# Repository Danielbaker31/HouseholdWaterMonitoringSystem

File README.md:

https://danielbaker31.github.io/HouseholdWaterMonitoringSystem/

This is a work in progress.

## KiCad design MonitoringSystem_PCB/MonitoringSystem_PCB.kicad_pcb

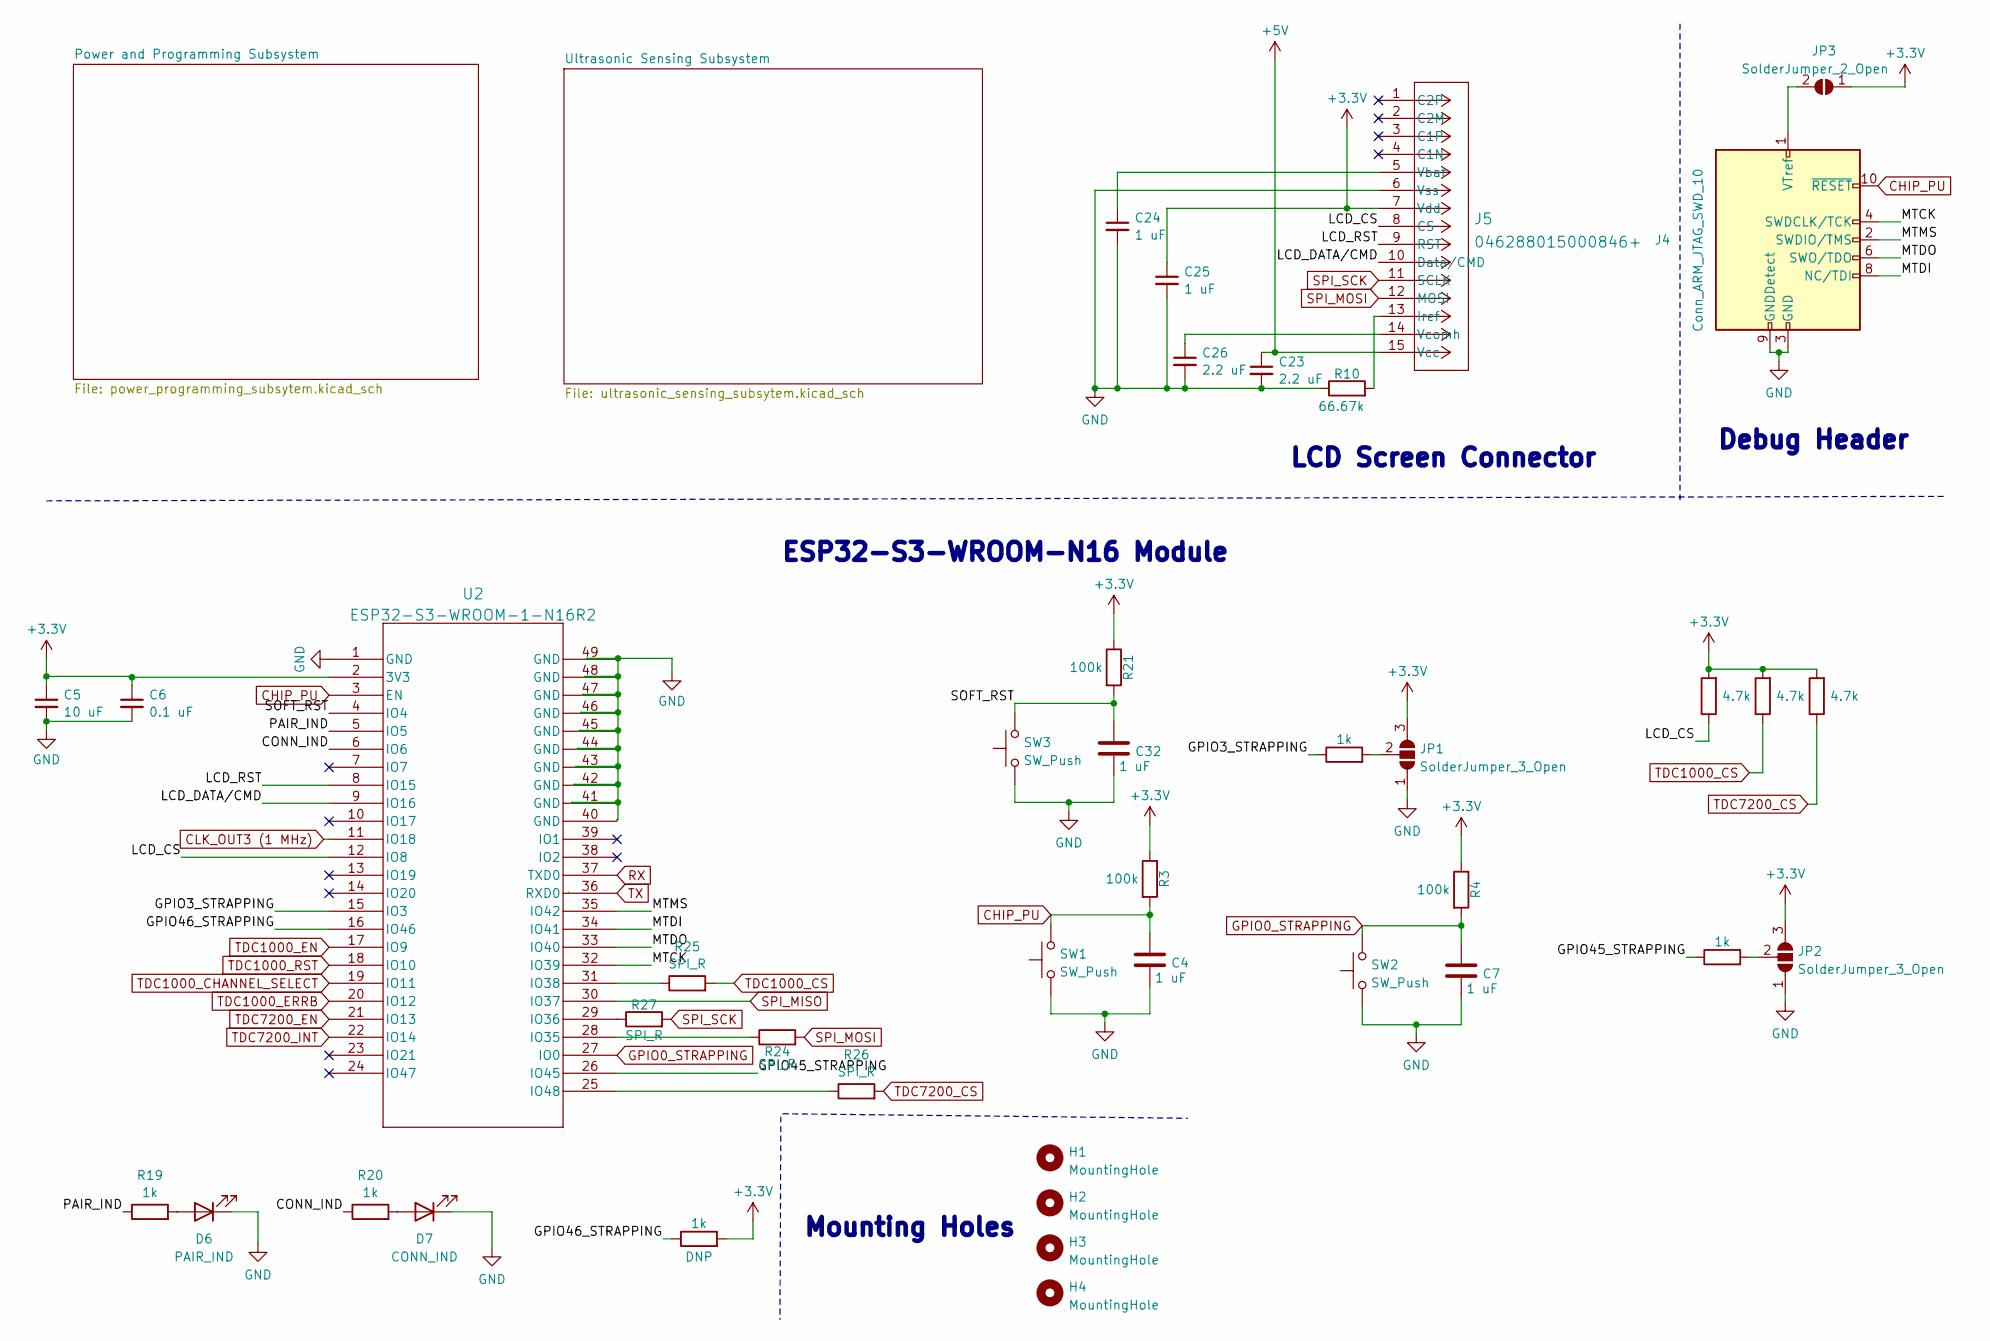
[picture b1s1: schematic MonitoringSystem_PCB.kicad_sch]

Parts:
C4, C7, C24, C25, C32: 1 uF; C_0805_2012Metric
C5: 10 uF; C_0805_2012Metric
C6: 0.1 uF; C_0805_2012Metric
C23, C26: 2.2 uF; C_0805_2012Metric
D6: PAIR_IND; LED_0805_2012Metric
D7: CONN_IND; LED_0805_2012Metric
H1, H2, H3, H4: MountingHole; MountingHole_3.2mm_M3
J4: Conn_ARM_JTAG_SWD_10; IDC-Header_2x05_P2.54mm_Vertical
J5: 046288015000846+; 15Pin_TAB
JP1, JP2: SolderJumper_3_Open; SolderJumper-3_P2.0mm_Open_TrianglePad1.0x1.5mm
JP3: SolderJumper_2_Open; SolderJumper-2_P1.3mm_Open_TrianglePad1.0x1.5mm
R3, R4, R21: 100k; R_0805_2012Metric
R5, R6, R9, R19, R20: 1k; R_0805_2012Metric
R10: 66.67k; R_0805_2012Metric
R11, R12, R13: 4.7k; R_0805_2012Metric
R24, R25, R26, R27: SPI_R; R_0805_2012Metric
SW1, SW2, SW3: SW_Push; SW_SPST_B3S-1000
U2: ESP32-S3-WROOM-1-N16R2; ESP32-S3-WROOM-1_EXP

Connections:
+3.3V: C5.1, C6.1, C25.1, J5.7 (Vdd), JP1.3 (B), JP2.3 (B), JP3.1 (A), R3.1, R4.1, R6.2, R11.2, R12.2, R13.2, R21.1, U2.2 (3V3); also elsewhere on the board
+5V: C23.1, J5.15 (Vcc); also elsewhere on the board
/CONN_IND: R20.1, U2.6 (IO6)
/GPIO3_STRAPPING: R5.1, U2.15 (IO3)
/GPIO45_STRAPPING: R9.1, U2.26 (IO45)
/GPIO46_STRAPPING: R6.1, U2.16 (IO46)
/LCD_CS: J5.8 (CS), R11.1, U2.12 (IO8)
/LCD_DATA/CMD: J5.10 (Data/CMD), U2.9 (IO16)
/LCD_RST: J5.9 (RST), U2.8 (IO15)
/MTCK: J4.4 (SWDCLK/TCK), U2.32 (IO39)
/MTDI: J4.8 (NC/TDI), U2.34 (IO41)
/MTDO: J4.6 (SWO/TDO), U2.33 (IO40)
/MTMS: J4.2 (SWDIO/TMS), U2.35 (IO42)
/PAIR_IND: R19.1, U2.5 (IO5)
/SOFT_RST: C32.1, R21.2, SW3.2, U2.4 (IO4)
CHIP_PU: C4.1, J4.10 (~RESET), R3.2, SW1.2, U2.3 (EN); also elsewhere on the board
CLK_OUT3 (1 MHz): U2.11 (IO18); also elsewhere on the board
GND: C4.2, C5.2, C6.2, C7.2, C23.2, C24.2, C25.2, C26.2, C32.2, D6.1 (K), D7.1 (K), J4.3 (GND), J4.5 (GND), J4.9 (GNDDetect), J5.6 (Vss), JP1.1 (A), JP2.1 (A), R10.1, SW1.1, SW2.1, SW3.1, U2.1 (GND), U2.40 (GND), U2.41 (GND), U2.42 (GND), U2.43 (GND), U2.44 (GND), U2.45 (GND), U2.46 (GND), U2.47 (GND), U2.48 (GND), U2.49 (GND); also elsewhere on the board
GPIO0_STRAPPING: C7.1, R4.2, SW2.2, U2.27 (IO0); also elsewhere on the board
unnamed: D6.2 (A), R19.2
unnamed: D7.2 (A), R20.2
unnamed: J4.1 (VTref), JP3.2 (B)
unnamed: J5.13 (Iref), R10.2
unnamed: C24.1, J5.5 (Vbat)
unnamed: C26.1, J5.14 (Vcomh)
unnamed: JP1.2 (C), R5.2
unnamed: JP2.2 (C), R9.2
unnamed: R24.1, U2.28 (IO35)
unnamed: R27.1, U2.29 (IO36)
unnamed: R25.1, U2.31 (IO38)
unnamed: R26.1, U2.25 (IO48)
RX: U2.37 (TXD0); also elsewhere on the board
SPI_MISO: U2.30 (IO37); also elsewhere on the board
SPI_MOSI: J5.12 (MOSI), R24.2; also elsewhere on the board
SPI_SCK: J5.11 (SCLK), R27.2; also elsewhere on the board
TDC1000_CHANNEL_SELECT: U2.19 (IO11); also elsewhere on the board
TDC1000_CS: R12.1, R25.2; also elsewhere on the board
TDC1000_EN: U2.17 (IO9); also elsewhere on the board
TDC1000_ERRB: U2.20 (IO12); also elsewhere on the board
TDC1000_RST: U2.18 (IO10); also elsewhere on the board
TDC7200_CS: R13.1, R26.2; also elsewhere on the board
TDC7200_EN: U2.21 (IO13); also elsewhere on the board
TDC7200_INT: U2.22 (IO14); also elsewhere on the board
TX: U2.36 (RXD0); also elsewhere on the board

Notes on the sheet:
Mounting Holes
LCD Screen Connector
Debug Header
ESP32-S3-WROOM-N16 Module

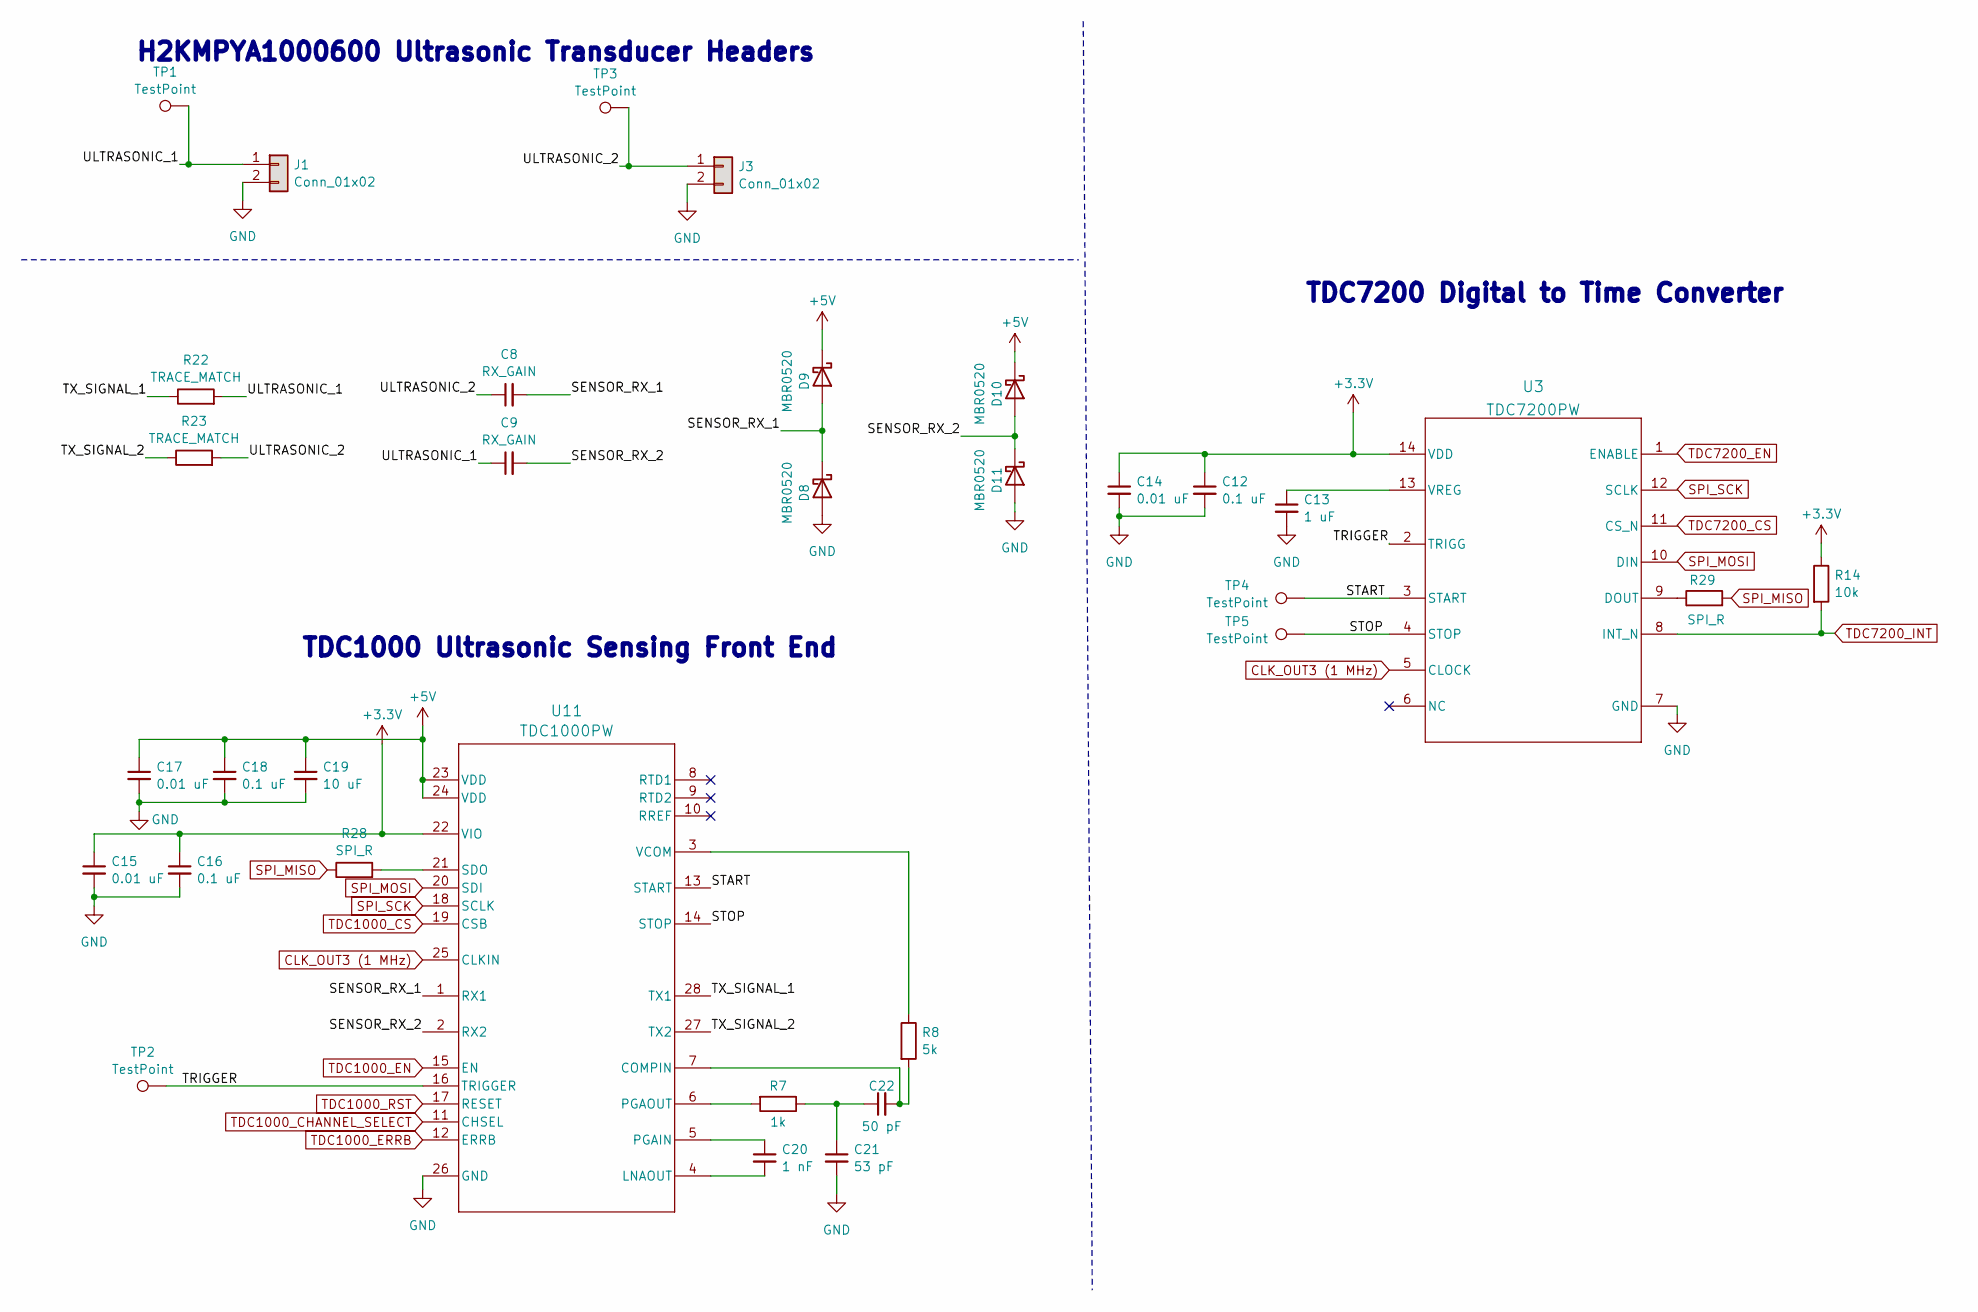
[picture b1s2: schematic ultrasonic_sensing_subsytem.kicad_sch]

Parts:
C8, C9: RX_GAIN; C_0805_2012Metric
C12, C16, C18: 0.1 uF; C_0805_2012Metric
C13: 1 uF; C_0805_2012Metric
C14, C15, C17: 0.01 uF; C_0805_2012Metric
C19: 10 uF; C_0805_2012Metric
C20: 1 nF; C_0805_2012Metric
C21: 53 pF; C_0805_2012Metric
C22: 50 pF; C_0805_2012Metric
D8, D9, D10, D11: MBR0520; D_SOD-123
J1, J3: Conn_01x02; Molex_KK-254_AE-6410-02A_1x02_P2.54mm_Vertical
R7: 1k; R_0805_2012Metric
R8: 5k; R_0805_2012Metric
R14: 10k; R_0805_2012Metric
R22, R23: TRACE_MATCH; R_0805_2012Metric
R28, R29: SPI_R; R_0805_2012Metric
TP1, TP2, TP3, TP4, TP5: TestPoint; TestPoint_Keystone_5010-5014_Multipurpose
U3: TDC7200PW; PW0014A_N
U11: TDC1000PW; PW0028A_N

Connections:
+3.3V: C12.1, C14.1, C15.1, C16.1, R14.1, U3.14 (VDD), U11.22 (VIO); also elsewhere on the board
+5V: C17.1, C18.1, C19.1, D9.1 (K), D10.1 (K), U11.23 (VDD), U11.24 (VDD); also elsewhere on the board
/Ultrasonic Sensing Subsystem/SENSOR_RX_1: C8.2, D8.1 (K), D9.2 (A), U11.1 (RX1)
/Ultrasonic Sensing Subsystem/SENSOR_RX_2: C9.2, D10.2 (A), D11.1 (K), U11.2 (RX2)
/Ultrasonic Sensing Subsystem/START: TP4.1, U3.3 (START), U11.13 (START)
/Ultrasonic Sensing Subsystem/STOP: TP5.1, U3.4 (STOP), U11.14 (STOP)
/Ultrasonic Sensing Subsystem/TRIGGER: TP2.1, U3.2 (TRIGG), U11.16 (TRIGGER)
/Ultrasonic Sensing Subsystem/TX_SIGNAL_1: R22.1, U11.28 (TX1)
/Ultrasonic Sensing Subsystem/TX_SIGNAL_2: R23.1, U11.27 (TX2)
/Ultrasonic Sensing Subsystem/ULTRASONIC_1: C9.1, J1.1, R22.2, TP1.1
/Ultrasonic Sensing Subsystem/ULTRASONIC_2: C8.1, J3.1, R23.2, TP3.1
CLK_OUT3 (1 MHz): U3.5 (CLOCK), U11.25 (CLKIN); also elsewhere on the board
GND: C12.2, C13.2, C14.2, C15.2, C16.2, C17.2, C18.2, C19.2, C21.2, D8.2 (A), D11.2 (A), J1.2, J3.2, U3.7 (GND), U11.26 (GND); also elsewhere on the board
unnamed: C21.1, C22.1, R7.1
unnamed: R29.1, U3.9 (DOUT)
unnamed: C13.1, U3.13 (VREG)
unnamed: C22.2, R8.2, U11.7 (COMPIN)
unnamed: C20.2, U11.4 (LNAOUT)
unnamed: C20.1, U11.5 (PGAIN)
unnamed: R7.2, U11.6 (PGAOUT)
unnamed: R28.2, U11.21 (SDO)
unnamed: R8.1, U11.3 (VCOM)
SPI_MISO: R28.1, R29.2; also elsewhere on the board
SPI_MOSI: U3.10 (DIN), U11.20 (SDI); also elsewhere on the board
SPI_SCK: U3.12 (SCLK), U11.18 (SCLK); also elsewhere on the board
TDC1000_CHANNEL_SELECT: U11.11 (CHSEL); also elsewhere on the board
TDC1000_CS: U11.19 (CSB); also elsewhere on the board
TDC1000_EN: U11.15 (EN); also elsewhere on the board
TDC1000_ERRB: U11.12 (ERRB); also elsewhere on the board
TDC1000_RST: U11.17 (RESET); also elsewhere on the board
TDC7200_CS: U3.11 (CS_N); also elsewhere on the board
TDC7200_EN: U3.1 (ENABLE); also elsewhere on the board
TDC7200_INT: R14.2, U3.8 (INT_N); also elsewhere on the board

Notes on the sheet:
H2KMPYA1000600 Ultrasonic Transducer Headers
TDC7200 Digital to Time Converter
TDC1000 Ultrasonic Sensing Front End

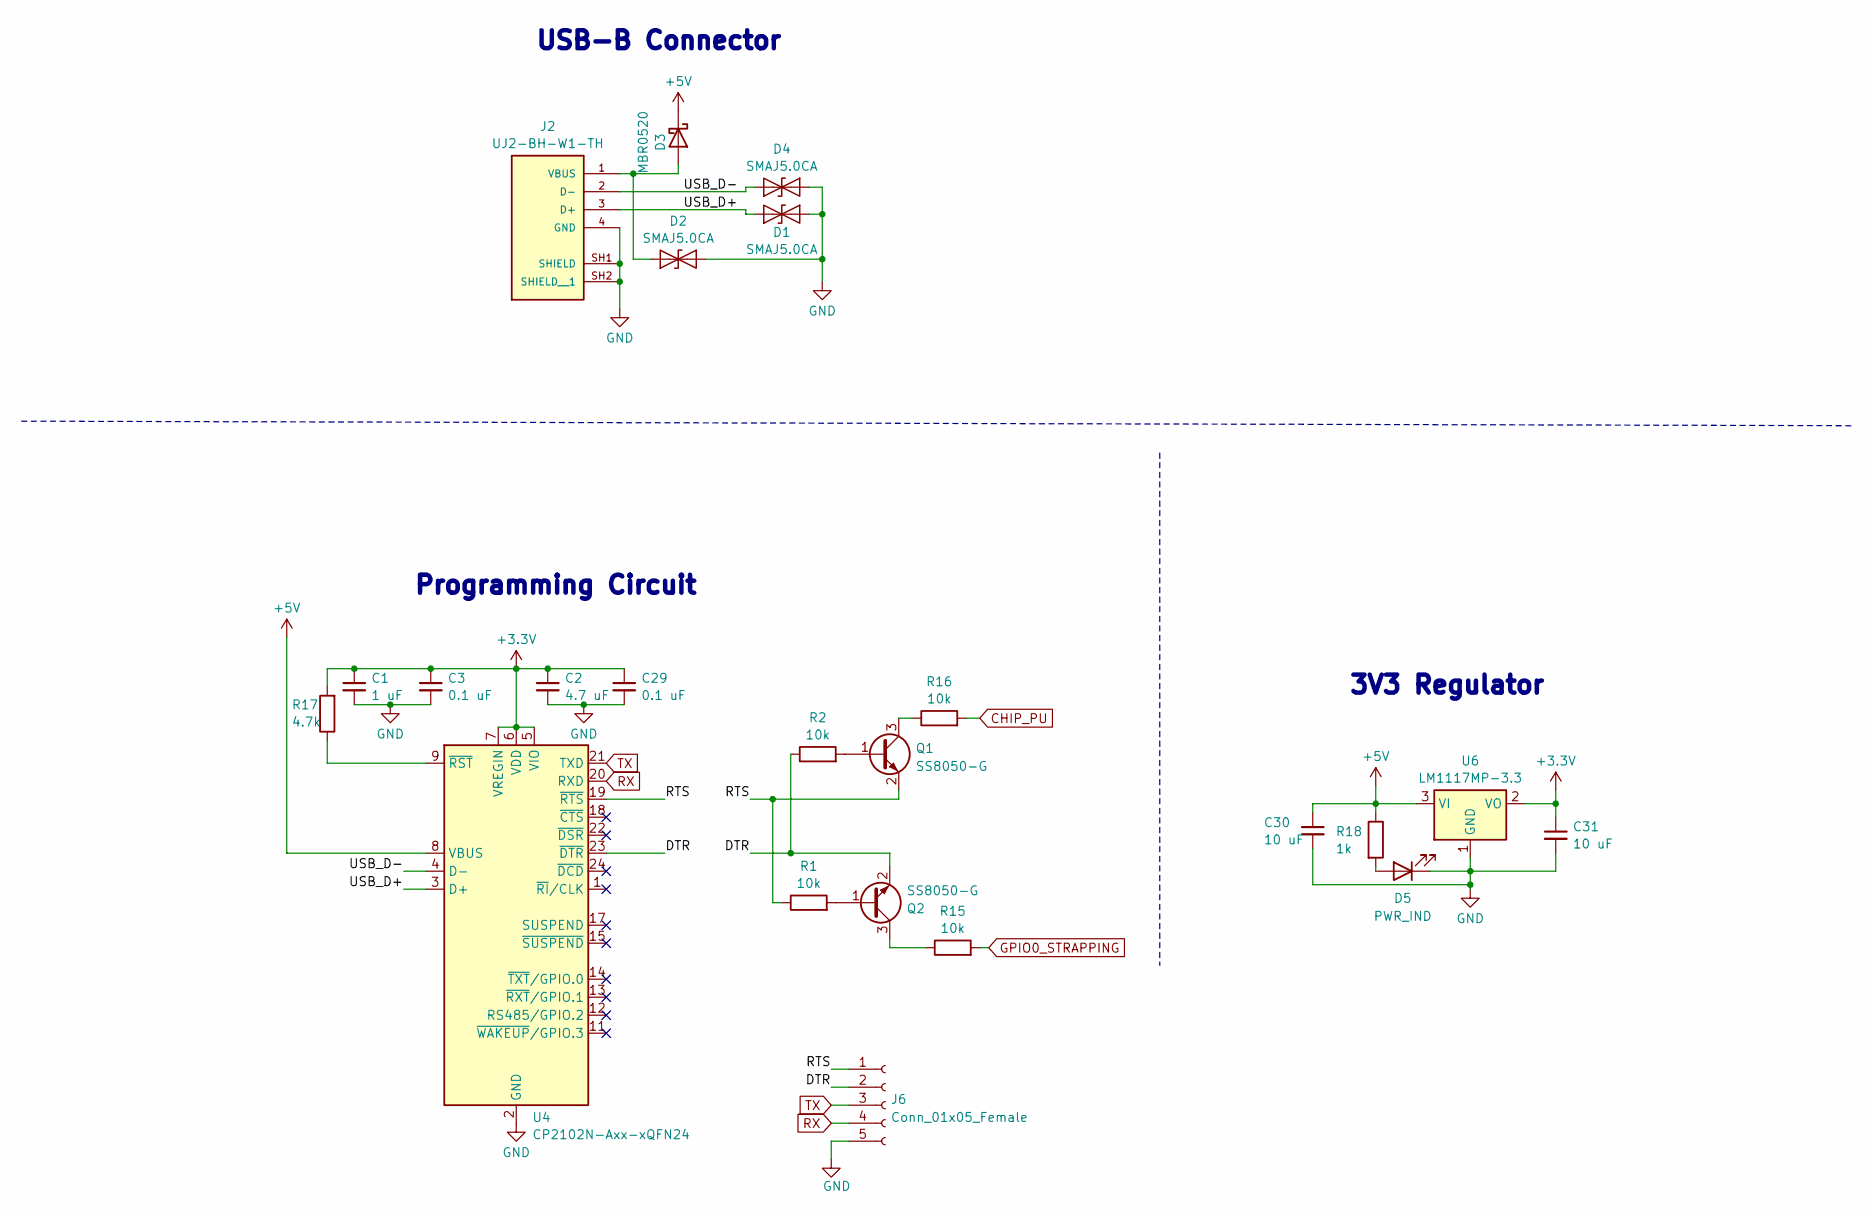
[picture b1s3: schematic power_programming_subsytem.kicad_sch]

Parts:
C1: 1 uF; C_0805_2012Metric
C2: 4.7 uF; C_0805_2012Metric
C3, C29: 0.1 uF; C_0805_2012Metric
C30, C31: 10 uF; C_0805_2012Metric
D1, D2, D4: SMAJ5.0CA; D_SMA
D3: MBR0520; D_SOD-123
D5: PWR_IND; LED_0805_2012Metric
J2: UJ2-BH-W1-TH; CUI_UJ2-BH-W1-TH; PART_REV 1.0
J6: Conn_01x05_Female; PinHeader_1x05_P2.54mm_Vertical
Q1, Q2: SS8050-G; SOT-23
R1, R2, R15, R16: 10k; R_0805_2012Metric
R17: 4.7k; R_0805_2012Metric
R18: 1k; R_0805_2012Metric
U4: CP2102N-Axx-xQFN24; QFN-24-1EP_4x4mm_P0.5mm_EP2.6x2.6mm
U6: LM1117MP-3.3; SOT-223-3_TabPin2

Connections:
+3.3V: C1.1, C2.1, C3.1, C29.1, C31.1, R17.2, U4.5 (VIO), U4.6 (VDD), U4.7 (VREGIN), U6.2 (VO); also elsewhere on the board
+5V: C30.1, D3.1 (K), R18.1, U4.8 (VBUS), U6.3 (VI); also elsewhere on the board
/Power and Programming Subsystem/DTR: J6.2, Q2.2 (E), R2.1, U4.23 (~DTR)
/Power and Programming Subsystem/RTS: J6.1, Q1.2 (E), R1.1, U4.19 (~RTS)
/Power and Programming Subsystem/USB_D+: D1.1 (A1), J2.3 (D+), U4.3 (D+)
/Power and Programming Subsystem/USB_D-: D4.1 (A1), J2.2 (D-), U4.4 (D-)
CHIP_PU: R16.2; also elsewhere on the board
GND: C1.2, C2.2, C3.2, C29.2, C30.2, C31.2, D1.2 (A2), D2.2 (A2), D4.2 (A2), D5.1 (K), J2.4 (GND), J2.SH1 (SHIELD), J2.SH2 (SHIELD__1), J6.5, U4.2 (GND), U4.25 (GND), U6.1 (GND); also elsewhere on the board
GPIO0_STRAPPING: R15.2; also elsewhere on the board
unnamed: D2.1 (A1), D3.2 (A), J2.1 (VBUS)
unnamed: D5.2 (A), R18.2
unnamed: Q1.1 (B), R2.2
unnamed: Q1.3 (C), R16.1
unnamed: Q2.1 (B), R1.2
unnamed: Q2.3 (C), R15.1
unnamed: R17.1, U4.9 (~RST)
RX: J6.4, U4.20 (RXD); also elsewhere on the board
TX: J6.3, U4.21 (TXD); also elsewhere on the board

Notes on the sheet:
Programming Circuit
3V3 Regulator
USB-B Connector

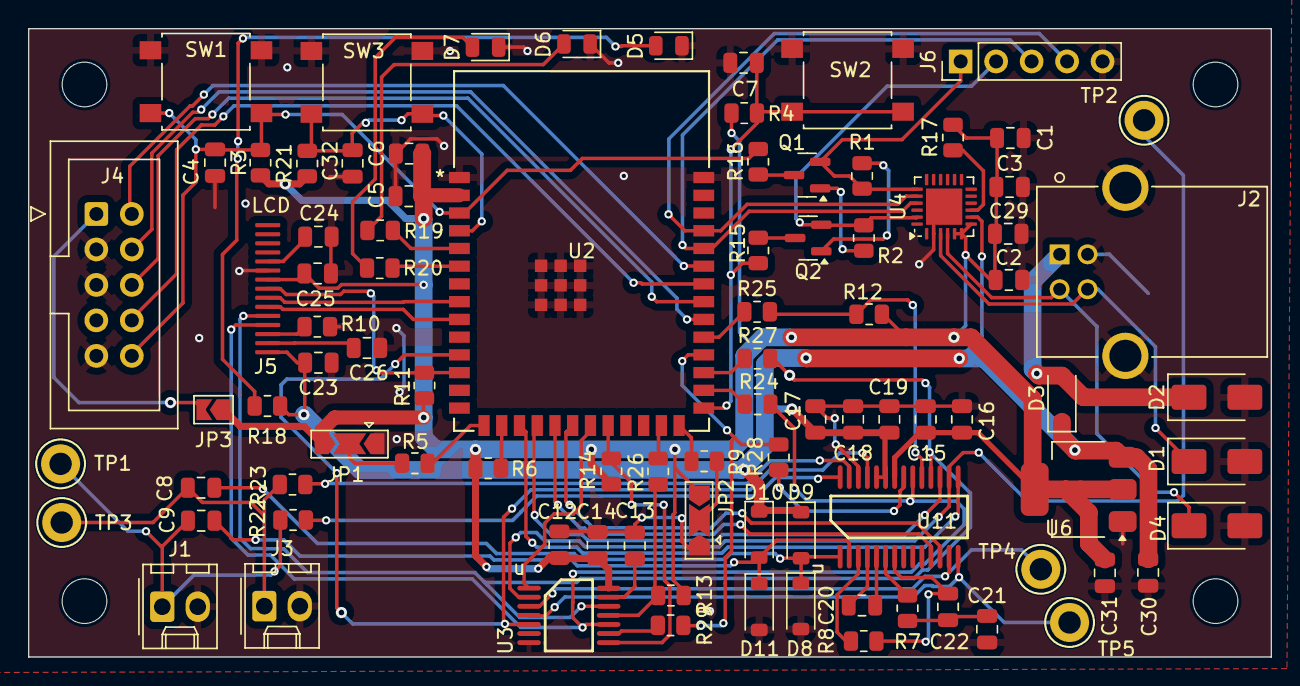
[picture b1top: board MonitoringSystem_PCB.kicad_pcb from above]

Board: 2 copper layers, 89.0 x 45.0 mm, 96 parts (0 on the bottom side), 73 nets.

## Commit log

2024-10-01 daniels journal
2024-10-02 drbaker5 journal thru 10/1
2024-10-02 week change
2024-10-09 adding advait journal
2024-10-10 github pages test
2024-10-10 moved index out of subfolder
2024-10-10 Create README.md
    added the website to the readme
2024-10-10 Mock Front End to test GET request
2024-10-10 updating display bug
2024-10-10 bug logging to see what's eerror
2024-10-10 fixing double parsing error
2024-10-11 first draft of pcb schematic
2024-10-11 modified parts' pinouts
2024-10-11 fix from backup
2024-10-11 redid project bc kicad is braindead
2024-10-11 schematic changes
2024-10-11 delete
2024-10-11 schematic updates
2024-10-15 finish first draft of schematic of PCB
2024-10-15 pushing complete frontend changes
2024-10-15 added multiple device registrion
2024-10-15 switched micro-usb for usb-b, started pcb
2024-10-15 minor change to usb-uart bridge
2024-10-15 fixed capitlaization bug
2024-10-15 fixing file name issues
2024-10-16 pcb done
2024-10-16 DRC error stuff
2024-10-16 finalized pcb, fixed eroors, generated gerber
2024-10-16 test commit
2024-10-17 Working frontend with registering device capability
2024-10-17 removed old frontedn code
2024-10-17 changing gitHub pages source to adapt to React
2024-10-23 adding react updates
2024-10-23 :wq #
2024-10-29 BOM and minor pcb updates
2024-10-29 moved frontend to new Repo, deleting from this repo
2024-11-01 stuff
2024-11-13 most recent pcb
2024-12-12 reformat journal
2024-12-12 sperate
2024-12-12 journal revision
2024-12-12 finalized journal
2024-12-12 fixed table of contents
2024-12-12 spelling and grammar mistakes
2024-12-12 finished notebook
2024-12-12 minor changes
